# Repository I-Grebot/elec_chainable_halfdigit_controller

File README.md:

# Chainable half-digit controller

## Requirements

Files inside `3d_models` folder must be copied into `<kicad dir>\share\kicad\modules\packages3d`

## Resources

Arduino Nano library downloaded from http://sylvain.fish.free.fr/kicad_lib/

NRF24L01 library downloaded from https://github.com/mysensors-kicad/mysensors_symbols

NRF24L01 footprint downloaded from https://github.com/mysensors-kicad/mysensors_radios.pretty

NRF24L01 3d model downloaded from https://github.com/mysensors-kicad/mysensors.3dshapes

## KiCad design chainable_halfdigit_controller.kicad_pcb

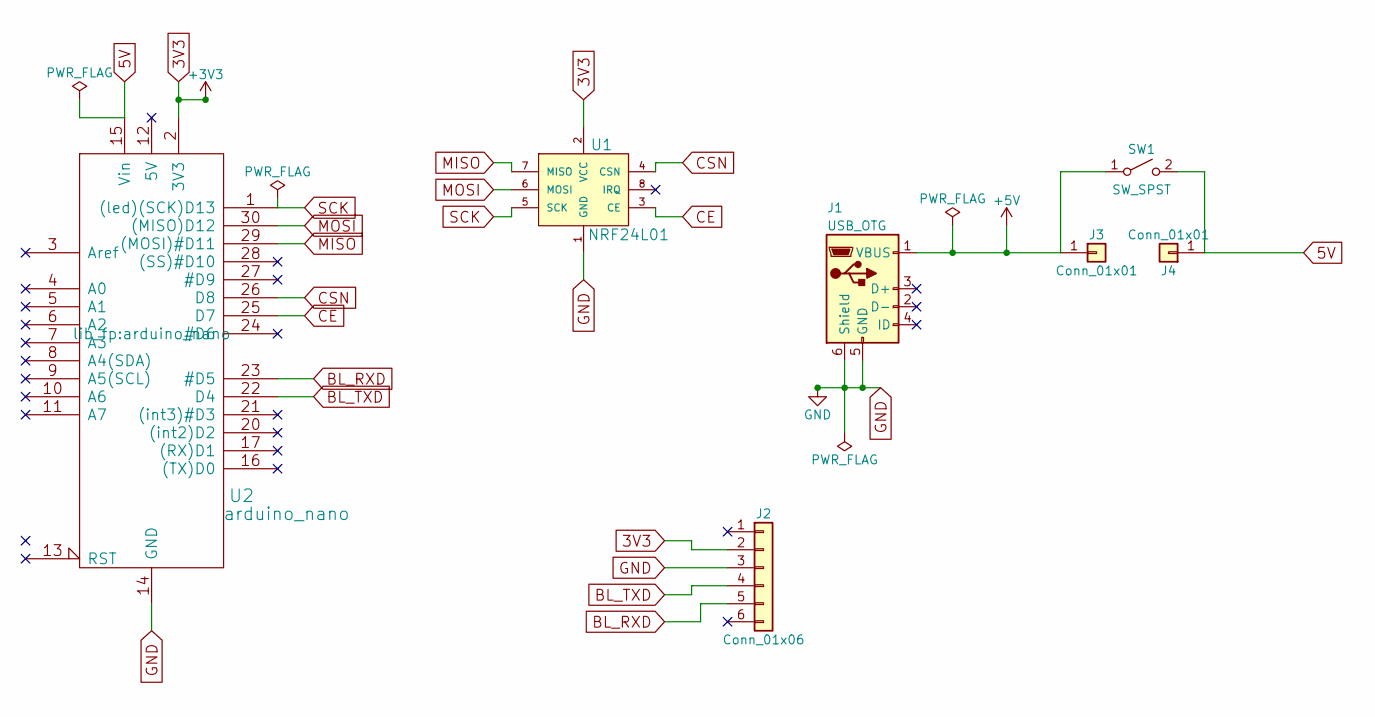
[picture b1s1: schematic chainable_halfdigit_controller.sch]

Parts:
J1: USB_OTG; ST-USB-013A
J2: Conn_01x06; Socket_Strip_Angled_1x06_Pitch2.54mm
J3, J4: Conn_01x01; Banana_Jack_1Pin
SW1: SW_SPST; Pin_Header_Straight_1x02_Pitch2.54mm
U1: NRF24L01
U2: arduino_nano

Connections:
3V3: J2.2, U1.2 (VCC), U2.2 (3V3)
5V: J4.1, SW1.2 (B), U2.15 (Vin)
+5V: J1.1 (VBUS), J3.1, SW1.1 (A)
BL_RXD: J2.5, U2.23 (#D5)
BL_TXD: J2.4, U2.22 (D4)
CE: U1.3 (CE), U2.25 (D7)
CSN: U1.4 (CSN), U2.26 (D8)
GND: J1.5 (GND), J1.6 (Shield), J2.3, U1.1 (GND), U2.14 (GND), U2.19 (GND)
MISO: U1.7 (MISO), U2.29 ((MOSI)#D11)
MOSI: U1.6 (MOSI), U2.30 ((MISO)D12)
SCK: U1.5 (SCK), U2.1 ((led)(SCK)D13)

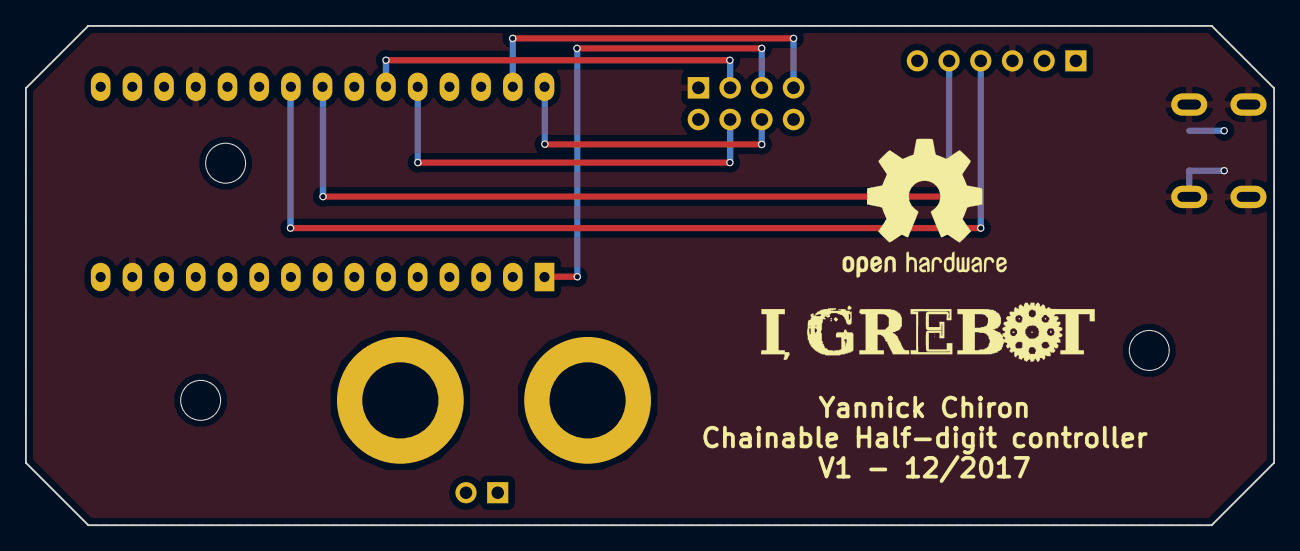
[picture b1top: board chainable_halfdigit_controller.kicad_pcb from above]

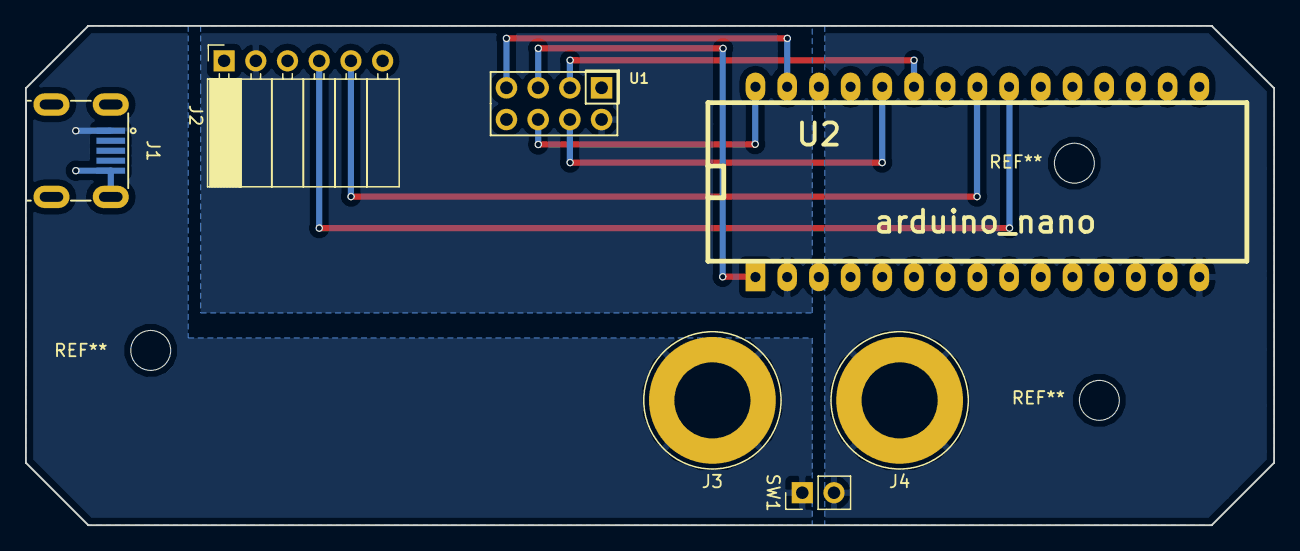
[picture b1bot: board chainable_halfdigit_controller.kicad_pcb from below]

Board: 2 copper layers, 100.0 x 40.0 mm, 7 parts (7 on the bottom side), 11 nets.

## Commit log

2017-11-27 Added Arduino nano, NRF24L01 and USB connector
2017-11-27 Added resources links to README.md
2017-11-27 Fixed README.md formating
2017-11-27 Added Requirements section to README.md
2017-11-28 Made custom ST-USB-013A footprint for mini usb connector
2017-11-28 Added bluetooth connection, board outline and mounting holes
2017-11-30 Fixed ST-USB-013A pad sizes, added a mounting hole, added missing tracks
2017-11-30 Added info and logo, exported plot
2017-12-01 Fixed card name
2017-12-02 Added banana jack and pin header for power switch
2017-12-02 Exported gerber
2017-12-09 Fixed DRC errors
2017-12-17 Added via near USB GND pin
2017-12-17 Updated plot with latest changes
2018-01-04 Added Arduino and Unity projects
2018-01-04 Fixed README.md with new folder organization
2018-01-15 Fixed led timings and moved digit func outside of critially timed code
2018-05-02 Add solidworks casing
2018-05-02 Add DXF cut groups
2018-05-05 Adaptation Arduino
2018-05-07 Fix port for Arduino Nano pro
2018-05-07 Add draft for bluetooth communication
2018-05-09 Read score from bluetooth
2018-05-19 CDR implementation
